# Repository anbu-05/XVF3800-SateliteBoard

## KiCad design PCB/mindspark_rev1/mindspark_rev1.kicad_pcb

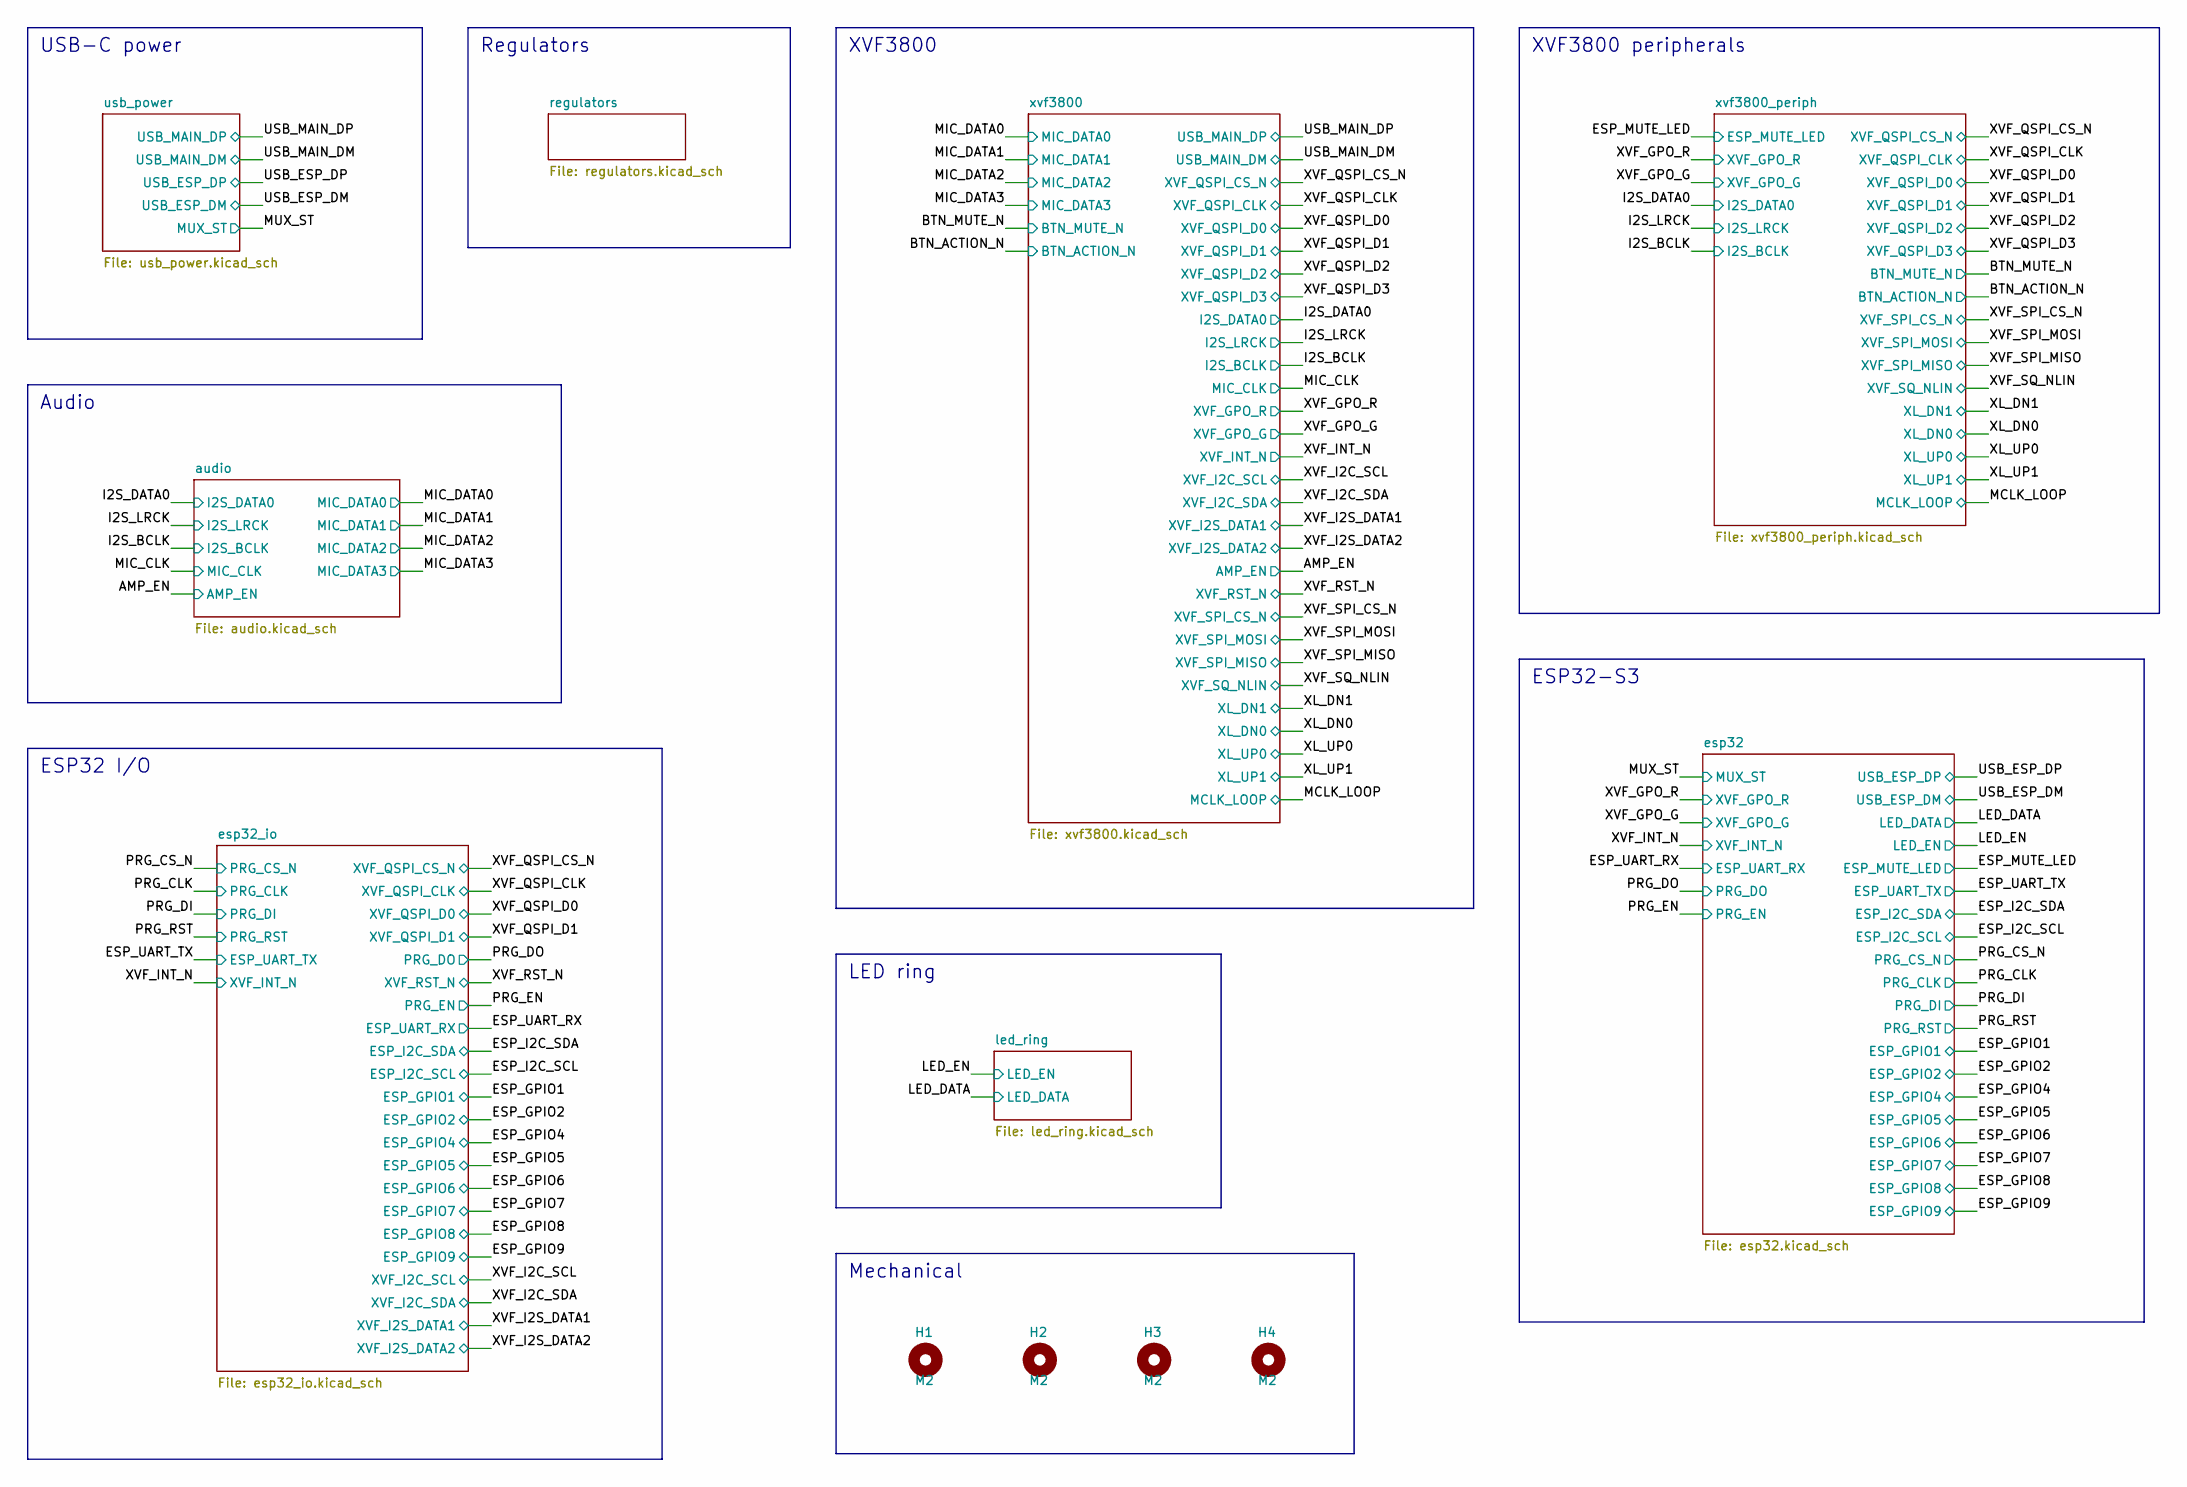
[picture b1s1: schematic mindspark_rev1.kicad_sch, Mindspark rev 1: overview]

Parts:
H1, H2, H3, H4: M2; MountingHole_2.2mm_M2_Pad_Via

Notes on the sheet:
Audio
LED ring
XVF3800
XVF3800 peripherals
Mechanical
Regulators
ESP32-S3
ESP32 I/O
USB-C power

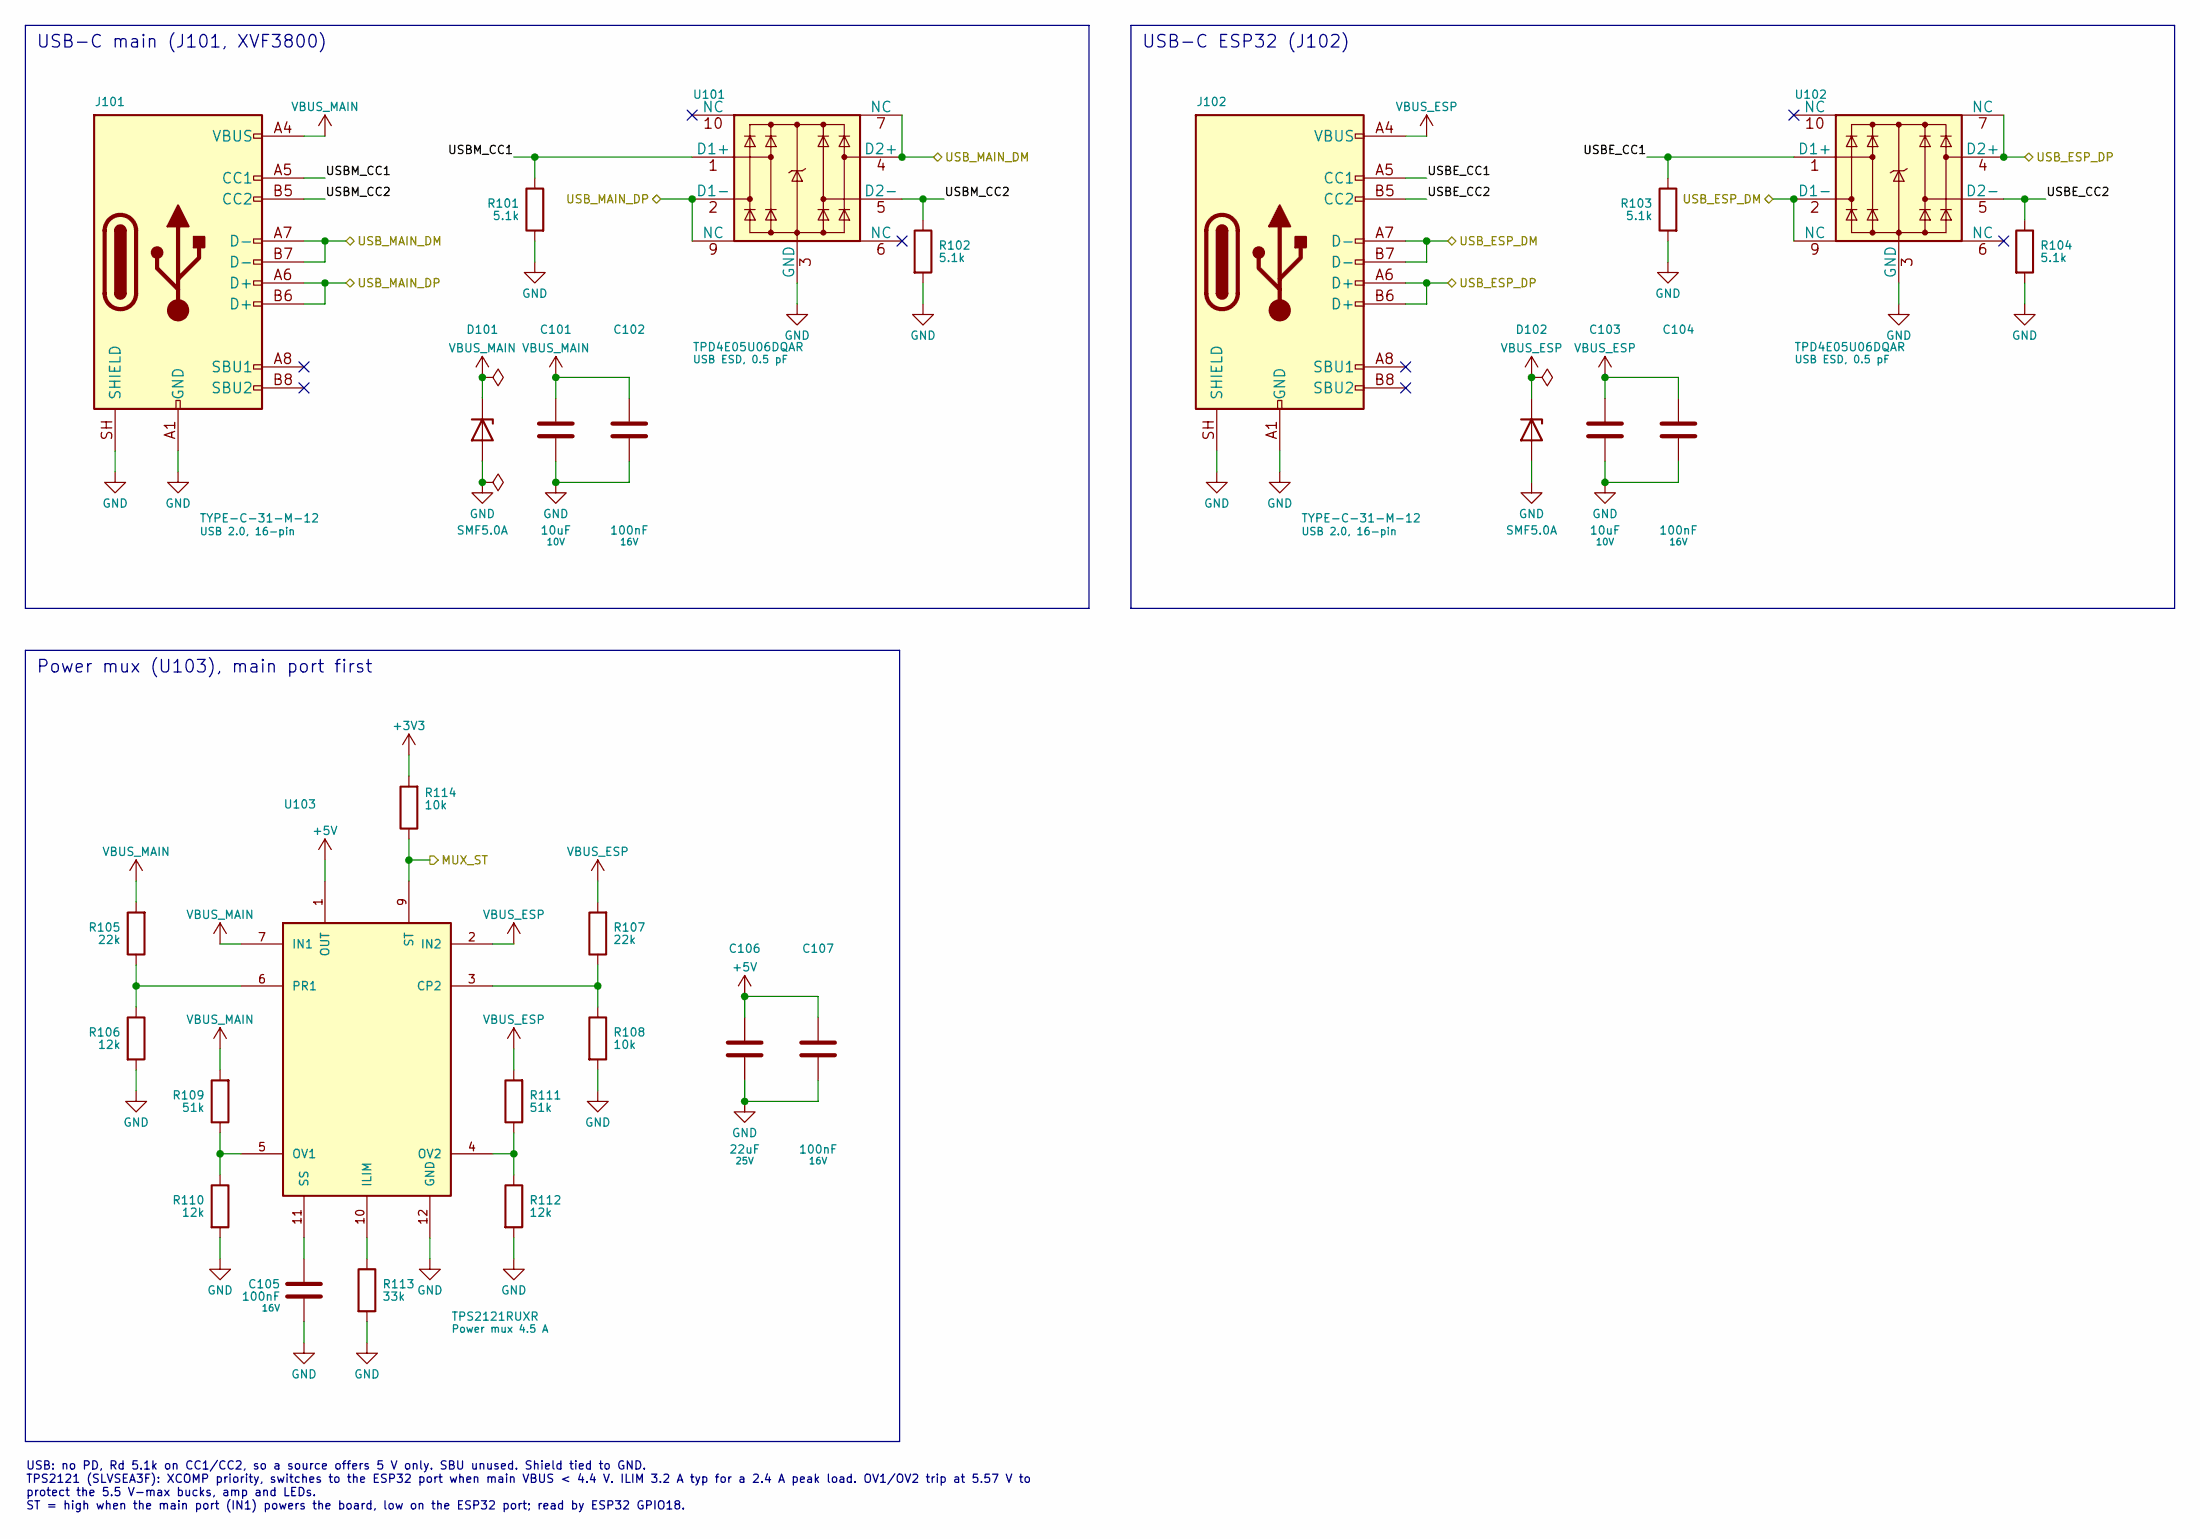
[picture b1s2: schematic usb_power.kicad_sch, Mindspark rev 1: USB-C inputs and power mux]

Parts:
C101, C103: 10uF; C_0603_1608Metric; voltage 10V; MPN CL10A106KP8NNNC; LCSC C19702
C102, C104, C105, C107: 100nF; C_0402_1005Metric; voltage 16V; MPN CL05B104KO5NNNC; LCSC C1525
C106: 22uF; C_0805_2012Metric; voltage 25V; MPN CL21A226MAQNNNE; LCSC C45783
D101, D102: SMF5.0A; D_SMF; MPN SMF5.0A; LCSC C193402
J101, J102: TYPE-C-31-M-12; USB_C_Receptacle_HRO_TYPE-C-31-M-12; MPN TYPE-C-31-M-12; LCSC C165948
R101, R102, R103, R104: 5.1k; R_0402_1005Metric; tolerance 1%; MPN 0402WGF5101TCE; LCSC C25905
R105, R107: 22k; R_0402_1005Metric; tolerance 1%; MPN 0402WGF2202TCE; LCSC C25768
R106, R110, R112: 12k; R_0402_1005Metric; tolerance 1%; MPN 0402WGF1202TCE; LCSC C25752
R108, R114: 10k; R_0402_1005Metric; tolerance 1%; MPN 0402WGF1002TCE; LCSC C25744
R109, R111: 51k; R_0402_1005Metric; tolerance 1%; MPN 0402WGF5102TCE; LCSC C25794
R113: 33k; R_0402_1005Metric; tolerance 1%; MPN 0402WGF3302TCE; LCSC C25779
U101, U102: TPD4E05U06DQAR; USON-10_2.5x1.0mm_P0.5mm; MPN TPD4E05U06DQAR; LCSC C138714
U103: TPS2121RUXR; TI_RUX0012A_VQFN-HR-12_2x2.5mm; MPN TPS2121RUXR; LCSC C485916

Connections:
+3V3: R114.2; also elsewhere on the board
+5V: C106.1, C107.1, U103.1 (OUT), U103.8 (OUT); also elsewhere on the board
/MUX_ST: R114.1, U103.9 (ST); also elsewhere on the board
/USB_ESP_DM: J102.A7 (D-), J102.B7 (D-), U102.2 (D1-), U102.9 (NC); also elsewhere on the board
/USB_ESP_DP: J102.A6 (D+), J102.B6 (D+), U102.4 (D2+), U102.7 (NC); also elsewhere on the board
/USB_MAIN_DM: J101.A7 (D-), J101.B7 (D-), U101.4 (D2+), U101.7 (NC); also elsewhere on the board
/USB_MAIN_DP: J101.A6 (D+), J101.B6 (D+), U101.2 (D1-), U101.9 (NC); also elsewhere on the board
/usb_power/USBE_CC1: J102.A5 (CC1), R103.1, U102.1 (D1+)
/usb_power/USBE_CC2: J102.B5 (CC2), R104.1, U102.5 (D2-)
/usb_power/USBM_CC1: J101.A5 (CC1), R101.1, U101.1 (D1+)
/usb_power/USBM_CC2: J101.B5 (CC2), R102.1, U101.5 (D2-)
GND: C101.2, C102.2, C103.2, C104.2, C105.2, C106.2, C107.2, D101.2 (A), D102.2 (A), J101.A1 (GND), J101.A12 (GND), J101.B1 (GND), J101.B12 (GND), J101.SH (SHIELD), J102.A1 (GND), J102.A12 (GND), J102.B1 (GND), J102.B12 (GND), J102.SH (SHIELD), R101.2, R102.2, R103.2, R104.2, R106.2, R108.2, R110.2, R112.2, R113.2, U101.3 (GND), U101.8 (GND), U102.3 (GND), U102.8 (GND), U103.12 (GND); also elsewhere on the board
unnamed: R107.1, R108.1, U103.3 (CP2)
unnamed: R113.1, U103.10 (ILIM)
unnamed: R109.1, R110.1, U103.5 (OV1)
unnamed: R111.1, R112.1, U103.4 (OV2)
unnamed: R105.1, R106.1, U103.6 (PR1)
unnamed: C105.1, U103.11 (SS)
VBUS_ESP: C103.1, C104.1, D102.1 (K), J102.A4 (VBUS), J102.A9 (VBUS), J102.B4 (VBUS), J102.B9 (VBUS), R107.2, R111.2, U103.2 (IN2)
VBUS_MAIN: C101.1, C102.1, D101.1 (K), J101.A4 (VBUS), J101.A9 (VBUS), J101.B4 (VBUS), J101.B9 (VBUS), R105.2, R109.2, U103.7 (IN1)

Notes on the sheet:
USB-C main (J101, XVF3800)
USB-C ESP32 (J102)
USB: no PD, Rd 5.1k on CC1/CC2, so a source offers 5 V only. SBU unused. Shield tied to GND. TPS2121 (SLVSEA3F): XCOMP priority, switches to the ESP32 port when main VBUS < 4.4 V. ILIM 3.2 A typ for a 2.4 A peak load. OV1/OV2 trip at 5.57 V to protect the 5.5 V-max bucks, amp and LEDs. ST = high wh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
Power mux (U103), main port first

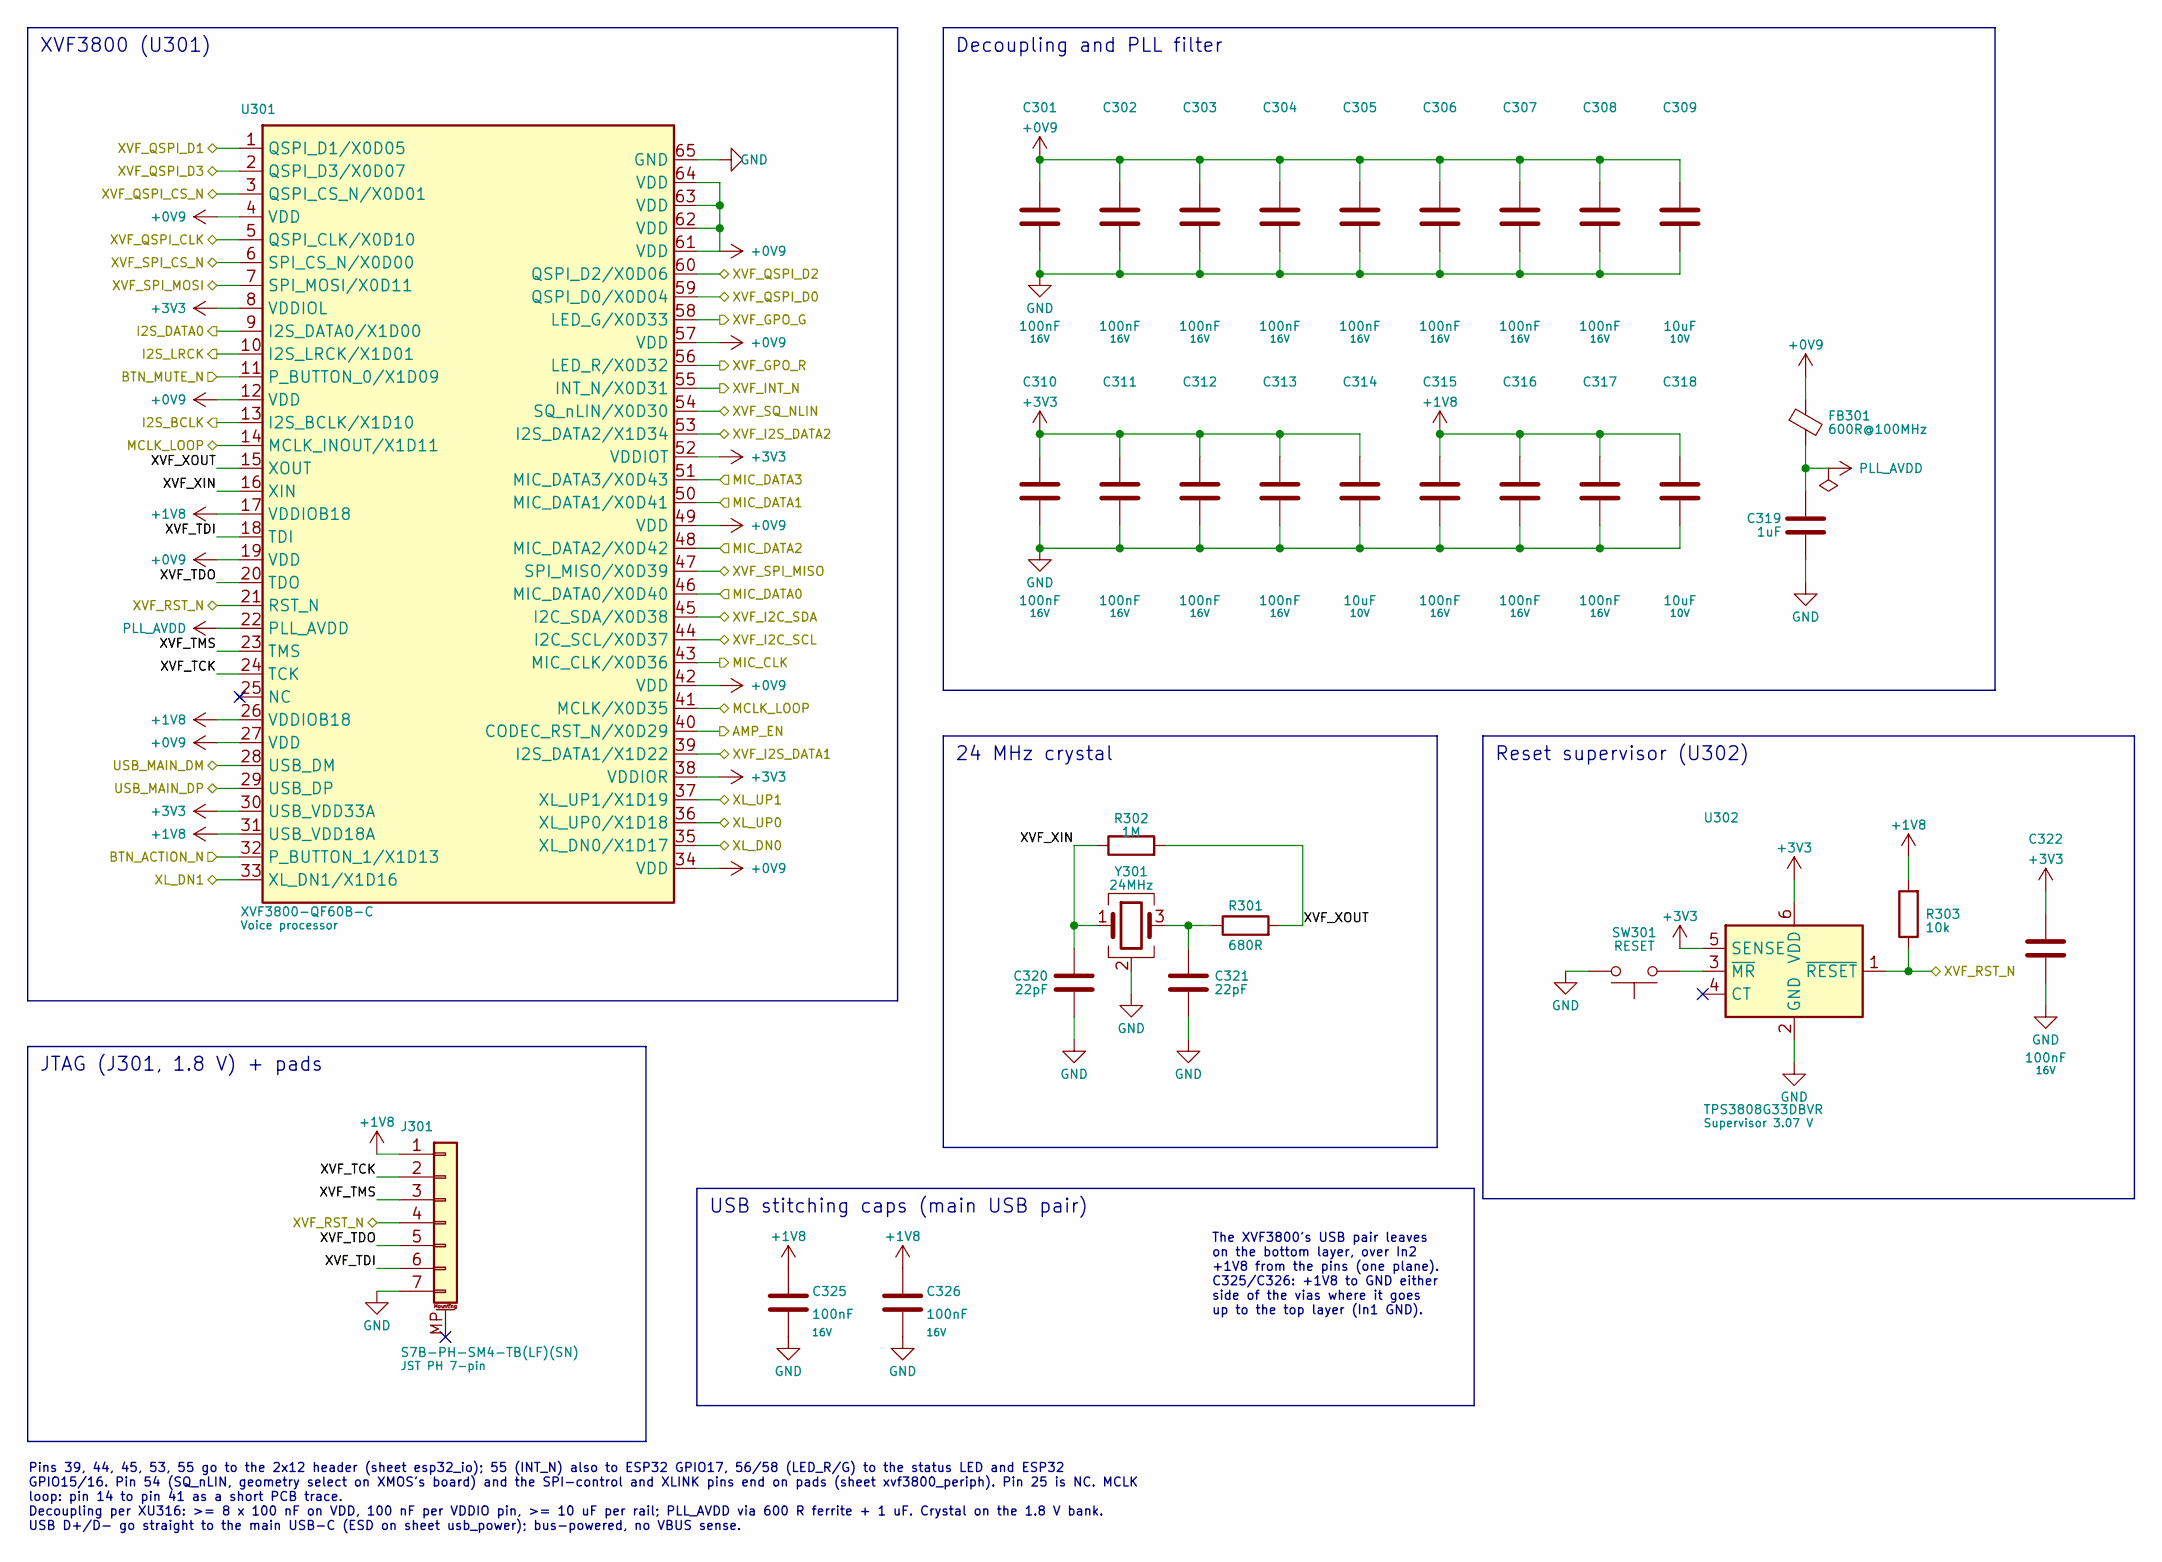
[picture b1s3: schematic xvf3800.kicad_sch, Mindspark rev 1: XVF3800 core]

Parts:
C301, C302, C303, C304, C305, C306, C307, C308, C310, C311, C312, C313, C315, C316, C317, C322, C325, C326: 100nF; C_0402_1005Metric; voltage 16V; MPN CL05B104KO5NNNC; LCSC C1525
C309, C314, C318: 10uF; C_0603_1608Metric; voltage 10V; MPN CL10A106KP8NNNC; LCSC C19702
C319: 1uF; C_0402_1005Metric; voltage 25V; MPN CL05A105KA5NQNC; LCSC C52923
C320, C321: 22pF; C_0402_1005Metric; voltage 50V; MPN 0402CG220J500NT; LCSC C1555
FB301: 600R@100MHz; L_0402_1005Metric; MPN BLM15AG601SN1D; LCSC C76884
J301: S7B-PH-SM4-TB(LF)(SN); JST_PH_S7B-PH-SM4-TB_1x07-1MP_P2.00mm_Horizontal; MPN S7B-PH-SM4-TB(LF)(SN); LCSC C265453
R301: 680R; R_0402_1005Metric; tolerance 1%; MPN 0402WGF6800TCE; LCSC C25130
R302: 1M; R_0402_1005Metric; tolerance 1%; MPN 0402WGF1004TCE; LCSC C26083
R303: 10k; R_0402_1005Metric; tolerance 1%; MPN 0402WGF1002TCE; LCSC C25744
SW301: RESET; SW_Push_1P1T_XKB_TS-1187A; MPN TS-1187A-B-A-B; LCSC C318884
U301: XVF3800-QF60B-C; XMOS_QFN-60-5EP_7x7mm_P0.4mm; MPN XVF3800-QF60B-C; LCSC C20491135
U302: TPS3808G33DBVR; SOT-23-6; MPN TPS3808G33DBVR; LCSC C43698
Y301: 24MHz; Crystal_SMD_3225-4Pin_3.2x2.5mm; MPN X322524MOB4SI; LCSC C70590

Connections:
+0V9: C301.1, C302.1, C303.1, C304.1, C305.1, C306.1, C307.1, C308.1, C309.1, FB301.1, U301.4 (VDD), U301.12 (VDD), U301.19 (VDD), U301.27 (VDD), U301.34 (VDD), U301.42 (VDD), U301.49 (VDD), U301.57 (VDD), U301.61 (VDD), U301.62 (VDD), U301.63 (VDD), U301.64 (VDD); also elsewhere on the board
+1V8: C315.1, C316.1, C317.1, C318.1, C325.1, C326.1, J301.1, R303.2, U301.17 (VDDIOB18), U301.26 (VDDIOB18), U301.31 (USB_VDD18A); also elsewhere on the board
+3V3: C310.1, C311.1, C312.1, C313.1, C314.1, C322.1, U301.8 (VDDIOL), U301.30 (USB_VDD33A), U301.38 (VDDIOR), U301.52 (VDDIOT), U302.5 (SENSE), U302.6 (VDD); also elsewhere on the board
/AMP_EN: U301.40 (CODEC_RST_N/X0D29); also elsewhere on the board
/BTN_ACTION_N: U301.32 (P_BUTTON_1/X1D13); also elsewhere on the board
/BTN_MUTE_N: U301.11 (P_BUTTON_0/X1D09); also elsewhere on the board
/I2S_BCLK: U301.13 (I2S_BCLK/X1D10); also elsewhere on the board
/I2S_DATA0: U301.9 (I2S_DATA0/X1D00); also elsewhere on the board
/I2S_LRCK: U301.10 (I2S_LRCK/X1D01); also elsewhere on the board
/MCLK_LOOP: U301.14 (MCLK_INOUT/X1D11), U301.41 (MCLK/X0D35); also elsewhere on the board
/MIC_CLK: U301.43 (MIC_CLK/X0D36); also elsewhere on the board
/MIC_DATA0: U301.46 (MIC_DATA0/X0D40); also elsewhere on the board
/MIC_DATA1: U301.50 (MIC_DATA1/X0D41); also elsewhere on the board
/MIC_DATA2: U301.48 (MIC_DATA2/X0D42); also elsewhere on the board
/MIC_DATA3: U301.51 (MIC_DATA3/X0D43); also elsewhere on the board
/USB_MAIN_DM: U301.28 (USB_DM); also elsewhere on the board
/USB_MAIN_DP: U301.29 (USB_DP); also elsewhere on the board
/XL_DN0: U301.35 (XL_DN0/X1D17); also elsewhere on the board
/XL_DN1: U301.33 (XL_DN1/X1D16); also elsewhere on the board
/XL_UP0: U301.36 (XL_UP0/X1D18); also elsewhere on the board
/XL_UP1: U301.37 (XL_UP1/X1D19); also elsewhere on the board
/XVF_GPO_G: U301.58 (LED_G/X0D33); also elsewhere on the board
/XVF_GPO_R: U301.56 (LED_R/X0D32); also elsewhere on the board
/XVF_I2C_SCL: U301.44 (I2C_SCL/X0D37); also elsewhere on the board
/XVF_I2C_SDA: U301.45 (I2C_SDA/X0D38); also elsewhere on the board
/XVF_I2S_DATA1: U301.39 (I2S_DATA1/X1D22); also elsewhere on the board
/XVF_I2S_DATA2: U301.53 (I2S_DATA2/X1D34); also elsewhere on the board
/XVF_INT_N: U301.55 (INT_N/X0D31); also elsewhere on the board
/XVF_QSPI_CLK: U301.5 (QSPI_CLK/X0D10); also elsewhere on the board
/XVF_QSPI_CS_N: U301.3 (QSPI_CS_N/X0D01); also elsewhere on the board
/XVF_QSPI_D0: U301.59 (QSPI_D0/X0D04); also elsewhere on the board
/XVF_QSPI_D1: U301.1 (QSPI_D1/X0D05); also elsewhere on the board
/XVF_QSPI_D2: U301.60 (QSPI_D2/X0D06); also elsewhere on the board
/XVF_QSPI_D3: U301.2 (QSPI_D3/X0D07); also elsewhere on the board
/XVF_RST_N: J301.4, R303.1, U301.21 (RST_N), U302.1 (~RESET); also elsewhere on the board
/XVF_SPI_CS_N: U301.6 (SPI_CS_N/X0D00); also elsewhere on the board
/XVF_SPI_MISO: U301.47 (SPI_MISO/X0D39); also elsewhere on the board
/XVF_SPI_MOSI: U301.7 (SPI_MOSI/X0D11); also elsewhere on the board
/XVF_SQ_NLIN: U301.54 (SQ_nLIN/X0D30); also elsewhere on the board
/xvf3800/XVF_TCK: J301.2, U301.24 (TCK)
/xvf3800/XVF_TDI: J301.6, U301.18 (TDI)
/xvf3800/XVF_TDO: J301.5, U301.20 (TDO)
/xvf3800/XVF_TMS: J301.3, U301.23 (TMS)
/xvf3800/XVF_XIN: C320.1, R302.1, U301.16 (XIN), Y301.1
/xvf3800/XVF_XOUT: R301.2, R302.2, U301.15 (XOUT)
GND: C301.2, C302.2, C303.2, C304.2, C305.2, C306.2, C307.2, C308.2, C309.2, C310.2, C311.2, C312.2, C313.2, C314.2, C315.2, C316.2, C317.2, C318.2, C319.2, C320.2, C321.2, C322.2, C325.2, C326.2, J301.7, SW301.2, U301.65 (GND), U302.2 (GND), Y301.2 (G), Y301.4 (G); also elsewhere on the board
unnamed: C321.1, R301.1, Y301.3
unnamed: SW301.1, U302.3 (~MR)
PLL_AVDD: C319.1, FB301.2, U301.22 (PLL_AVDD)

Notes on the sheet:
XVF3800 (U301)
Decoupling and PLL filter
JTAG (J301, 1.8 V) + pads
24 MHz crystal
Pins 39, 44, 45, 53, 55 go to the 2x12 header (sheet esp32_io); 55 (INT_N) also to ESP32 GPIO17, 56/58 (LED_R/G) to the status LED and ESP32 GPIO15/16. Pin 54 (SQ_nLIN, geometry select on XMOS's board) and the SPI-control and XLINK pins end on pads (sheet xvf3800_periph). Pin 25 is NC. MCLK loop: p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
Reset supervisor (U302)
USB stitching caps (main USB pair)
The XVF3800's USB pair leaves on the bottom layer, over In2 +1V8 from the pins (one plane). C325/C326: +1V8 to GND either side of the vias where it goes up to the top layer (In1 GND).

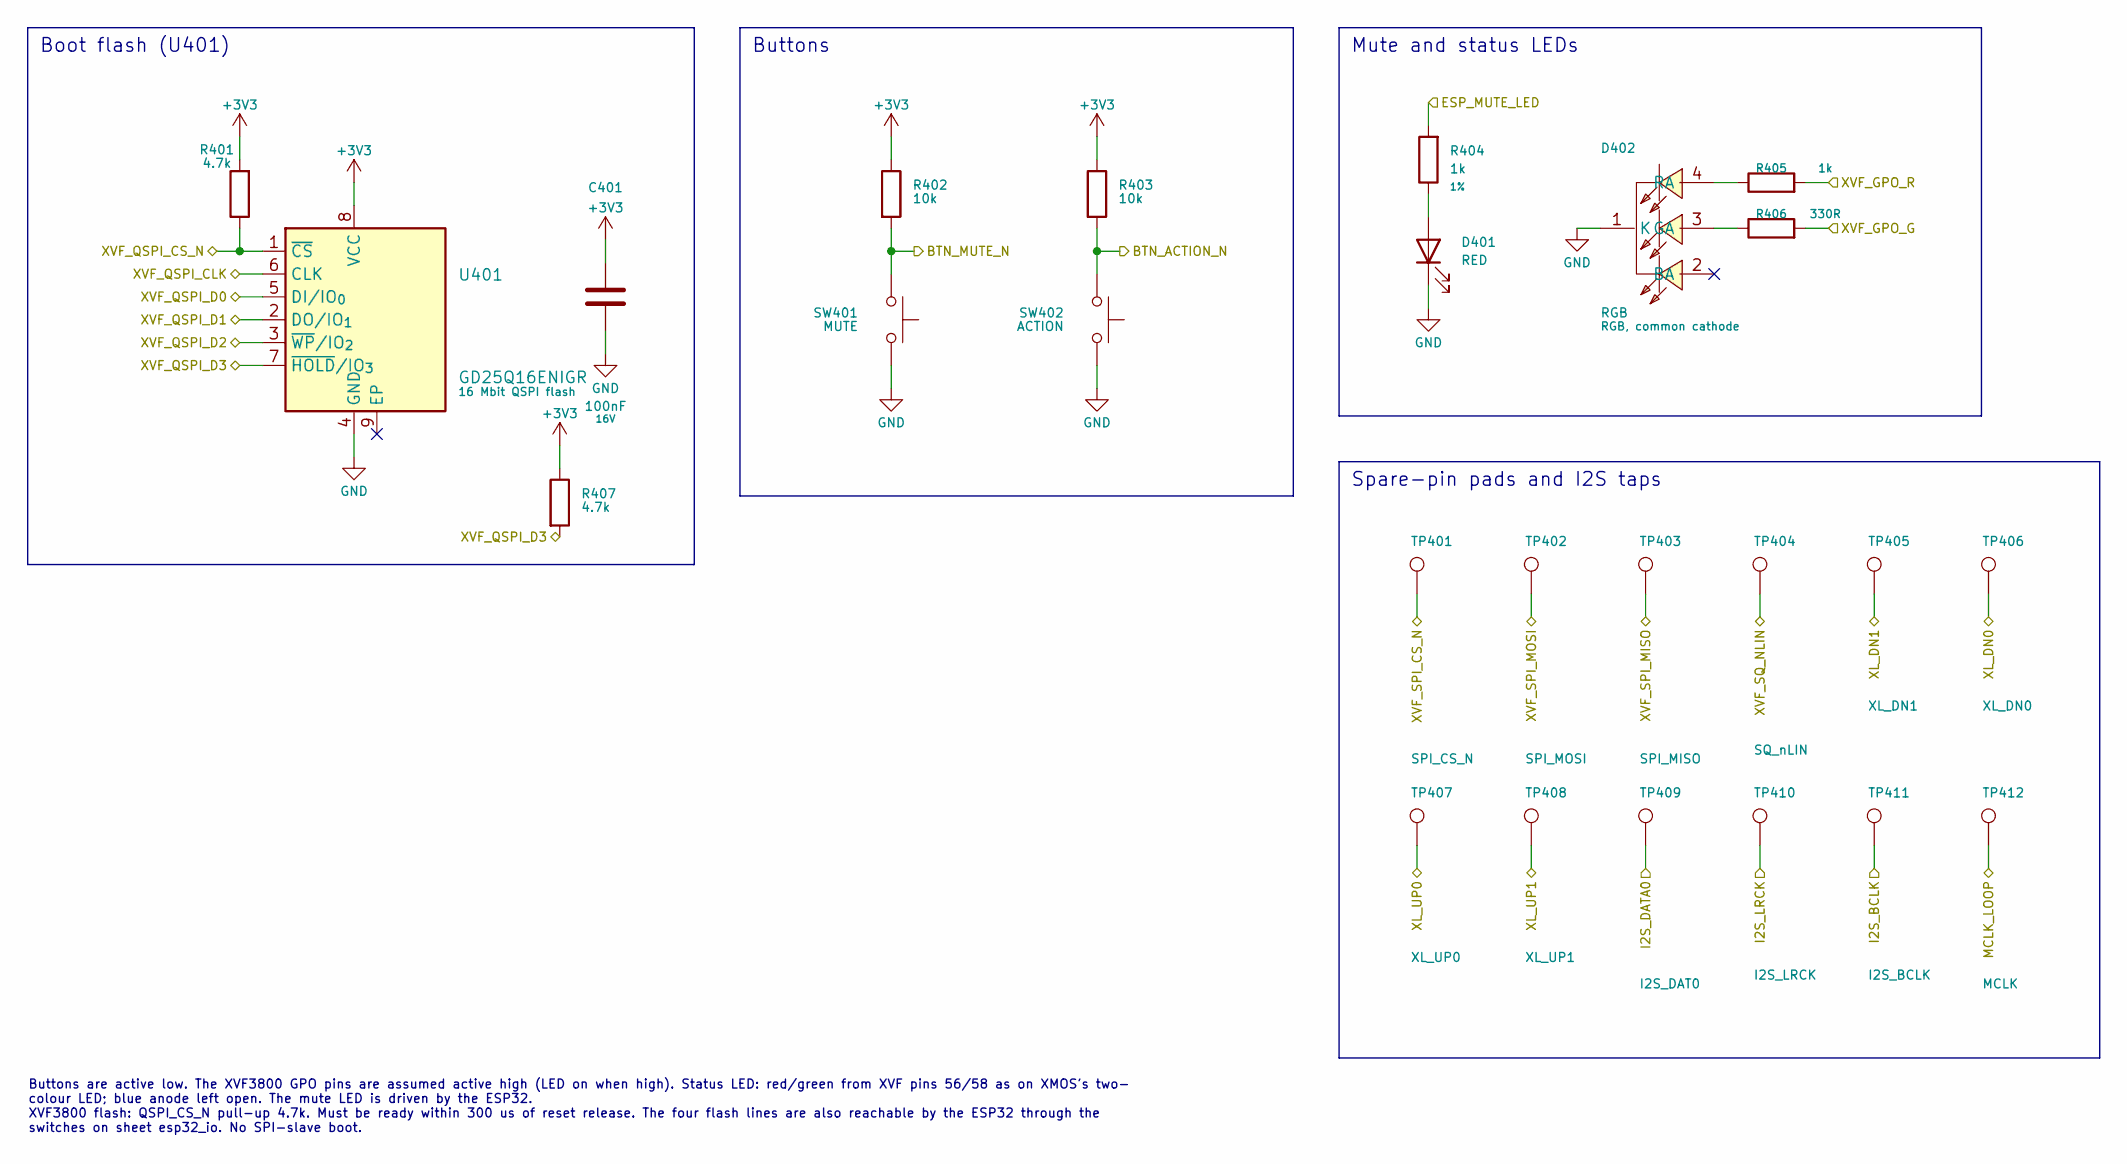
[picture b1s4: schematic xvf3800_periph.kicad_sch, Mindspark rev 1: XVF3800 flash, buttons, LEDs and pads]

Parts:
C401: 100nF; C_0402_1005Metric; voltage 16V; MPN CL05B104KO5NNNC; LCSC C1525
D401: RED; LED_0603_1608Metric; MPN KT-0603R; LCSC C2286
D402: RGB; LED_RGB_TOGIALED_1615_1.6x1.5mm; MPN TJ-S1615CY6TGLCCSRGB-A5; LCSC C601684
R401, R407: 4.7k; R_0402_1005Metric; tolerance 1%; MPN 0402WGF4701TCE; LCSC C25900
R402, R403: 10k; R_0402_1005Metric; tolerance 1%; MPN 0402WGF1002TCE; LCSC C25744
R404, R405: 1k; R_0402_1005Metric; tolerance 1%; MPN 0402WGF1001TCE; LCSC C11702
R406: 330R; R_0402_1005Metric; tolerance 1%; MPN 0402WGF3300TCE; LCSC C25104
SW401: MUTE; SW_SHOUHAN_TS24CA_SideActuated; MPN TS24CA; LCSC C393942
SW402: ACTION; SW_SHOUHAN_TS24CA_SideActuated; MPN TS24CA; LCSC C393942
TP401: SPI_CS_N; TestPoint_Pad_D1.0mm
TP402: SPI_MOSI; TestPoint_Pad_D1.0mm
TP403: SPI_MISO; TestPoint_Pad_D1.0mm
TP404: SQ_nLIN; TestPoint_Pad_D1.0mm
TP405: XL_DN1; TestPoint_Pad_D1.0mm
TP406: XL_DN0; TestPoint_Pad_D1.0mm
TP407: XL_UP0; TestPoint_Pad_D1.0mm
TP408: XL_UP1; TestPoint_Pad_D1.0mm
TP409: I2S_DAT0; TestPoint_Pad_D1.0mm
TP410: I2S_LRCK; TestPoint_Pad_D1.0mm
TP411: I2S_BCLK; TestPoint_Pad_D1.0mm
TP412: MCLK; TestPoint_Pad_D1.0mm
U401: GD25Q16ENIGR; Winbond_USON-8-2EP_3x4mm_P0.8mm_EP0.2x0.8mm; MPN GD25Q16ENIGR; LCSC C5749719

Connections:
+3V3: C401.1, R401.2, R402.1, R403.1, R407.1, U401.8 (VCC); also elsewhere on the board
/BTN_ACTION_N: R403.2, SW402.1; also elsewhere on the board
/BTN_MUTE_N: R402.2, SW401.1; also elsewhere on the board
/ESP_MUTE_LED: R404.2; also elsewhere on the board
/I2S_BCLK: TP411.1 (1_1); also elsewhere on the board
/I2S_DATA0: TP409.1 (1_1); also elsewhere on the board
/I2S_LRCK: TP410.1 (1_1); also elsewhere on the board
/MCLK_LOOP: TP412.1 (1_1); also elsewhere on the board
/XL_DN0: TP406.1 (1_1); also elsewhere on the board
/XL_DN1: TP405.1 (1_1); also elsewhere on the board
/XL_UP0: TP407.1 (1_1); also elsewhere on the board
/XL_UP1: TP408.1 (1_1); also elsewhere on the board
/XVF_GPO_G: R406.2; also elsewhere on the board
/XVF_GPO_R: R405.2; also elsewhere on the board
/XVF_QSPI_CLK: U401.6 (CLK); also elsewhere on the board
/XVF_QSPI_CS_N: R401.1, U401.1 (~CS); also elsewhere on the board
/XVF_QSPI_D0: U401.5 (DI/IO_{0}); also elsewhere on the board
/XVF_QSPI_D1: U401.2 (DO/IO_{1}); also elsewhere on the board
/XVF_QSPI_D2: U401.3 (~WP/IO_{2}); also elsewhere on the board
/XVF_QSPI_D3: R407.2, U401.7 (~HOLD/~RESET/IO_{3}); also elsewhere on the board
/XVF_SPI_CS_N: TP401.1 (1_1); also elsewhere on the board
/XVF_SPI_MISO: TP403.1 (1_1); also elsewhere on the board
/XVF_SPI_MOSI: TP402.1 (1_1); also elsewhere on the board
/XVF_SQ_NLIN: TP404.1 (1_1); also elsewhere on the board
GND: C401.2, D401.1 (K), D402.1 (K), SW401.2, SW402.2, U401.4 (GND); also elsewhere on the board
unnamed: D401.2 (A), R404.1
unnamed: D402.3 (GA), R406.1
unnamed: D402.4 (RA), R405.1

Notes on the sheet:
Spare-pin pads and I2S taps
Buttons are active low. The XVF3800 GPO pins are assumed active high (LED on when high). Status LED: red/green from XVF pins 56/58 as on XMOS's two- colour LED; blue anode left open. The mute LED is driven by the ESP32. XVF3800 flash: QSPI_CS_N pull-up 4.7k. Must be ready within 300 us of reset rel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
Mute and status LEDs
Buttons
Boot flash (U401)
